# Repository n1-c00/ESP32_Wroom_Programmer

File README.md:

# ESP32_Wroom_Programmer
This neat little board solves the issue always having a USB-UART Converter on your board when building a design with an ESP32. Some of you now may say "But this is just a simple USB-UART Converter I can get that on Aliexpress for a few €". But the thing that makes this sweet little board special, is that it has the auto-programming circuit from the ESP-Devboards. so by only exposing 5-6 Pins you can programm your custom PCB the same way you would do it on a Devkit (Plus it has USB-C but thats kinda the standard by now).

I hope you find it as usefull as me,
happy Building :)

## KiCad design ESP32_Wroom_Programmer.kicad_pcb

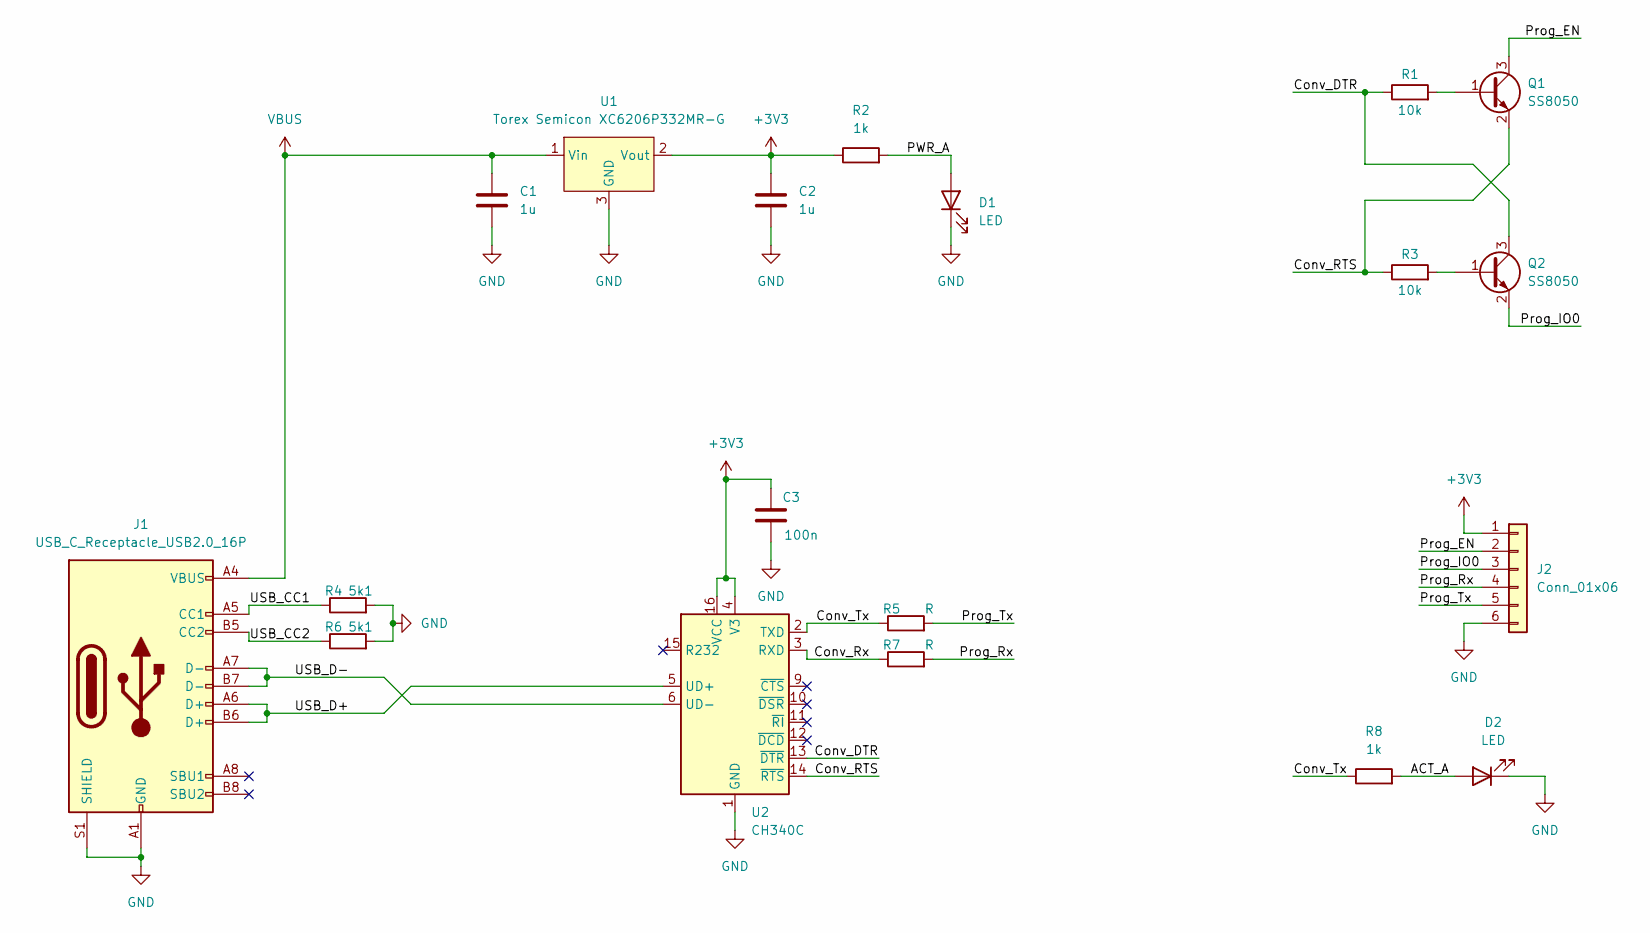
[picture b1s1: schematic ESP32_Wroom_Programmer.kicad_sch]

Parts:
C1, C2: 1u; C_0805_2012Metric
C3: 100n; C_0805_2012Metric
D1, D2: LED; LED_0805_2012Metric
J1: USB_C_Receptacle_USB2.0_16P; USB_C_Receptacle_GCT_USB4105-xx-A_16P_TopMnt_Horizontal
J2: Conn_01x06; PinHeader_1x06_P2.54mm_Horizontal
Q1, Q2: SS8050; SOT-23
R1, R3: 10k; R_0805_2012Metric
R2, R8: 1k; R_0805_2012Metric
R4, R6: 5k1; R_0603_1608Metric
R5, R7: R; R_0805_2012Metric
U1: Torex Semicon XC6206P332MR-G; SOT-23
U2: CH340C; SOIC-16_3.9x9.9mm_P1.27mm

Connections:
+3V3: C2.1, C3.1, J2.1, R2.1, U1.2 (Vout), U2.4 (V3), U2.16 (VCC)
/ACT_A: D2.2 (A), R8.2
/Conv_DTR: Q2.3 (C), R1.1, U2.13 (~DTR)
/Conv_RTS: Q1.2 (E), R3.1, U2.14 (~RTS)
/Conv_Rx: R7.1, U2.3 (RXD)
/Conv_Tx: R5.1, R8.1, U2.2 (TXD)
/PWR_A: D1.2 (A), R2.2
/Prog_EN: J2.2, Q1.3 (C)
/Prog_IO0: J2.3, Q2.2 (E)
/Prog_Rx: J2.4, R7.2
/Prog_Tx: J2.5, R5.2
/USB_CC1: J1.A5 (CC1), R4.1
/USB_CC2: J1.B5 (CC2), R6.1
/USB_D+: J1.A6 (D+), J1.B6 (D+), U2.5 (UD+)
/USB_D-: J1.A7 (D-), J1.B7 (D-), U2.6 (UD-)
GND: C1.2, C2.2, C3.2, D1.1 (K), D2.1 (K), J1.A1 (GND), J1.A12 (GND), J1.B1 (GND), J1.B12 (GND), J1.S1 (SHIELD), J2.6, R4.2, R6.2, U1.3 (GND), U2.1 (GND)
unnamed: Q1.1 (B), R1.2
unnamed: Q2.1 (B), R3.2
VBUS: C1.1, J1.A4 (VBUS), J1.A9 (VBUS), J1.B4 (VBUS), J1.B9 (VBUS), U1.1 (Vin)

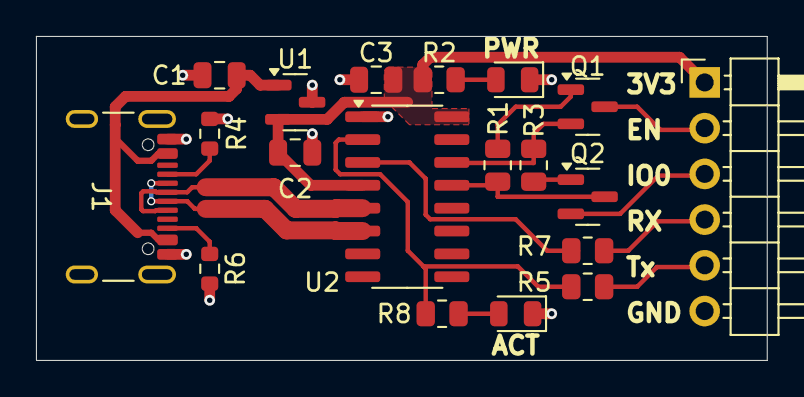
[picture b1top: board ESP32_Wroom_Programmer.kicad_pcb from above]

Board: 2 copper layers, 40.6 x 18.0 mm, 19 parts (0 on the bottom side), 19 nets.

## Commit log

2025-07-03 First commit!
2025-07-04 first version of PCB finished!
2025-07-04 fixed missing +3V3 connections
2025-07-04 there were still some connections missing...
2025-07-04 added ground to USB-C Shield
